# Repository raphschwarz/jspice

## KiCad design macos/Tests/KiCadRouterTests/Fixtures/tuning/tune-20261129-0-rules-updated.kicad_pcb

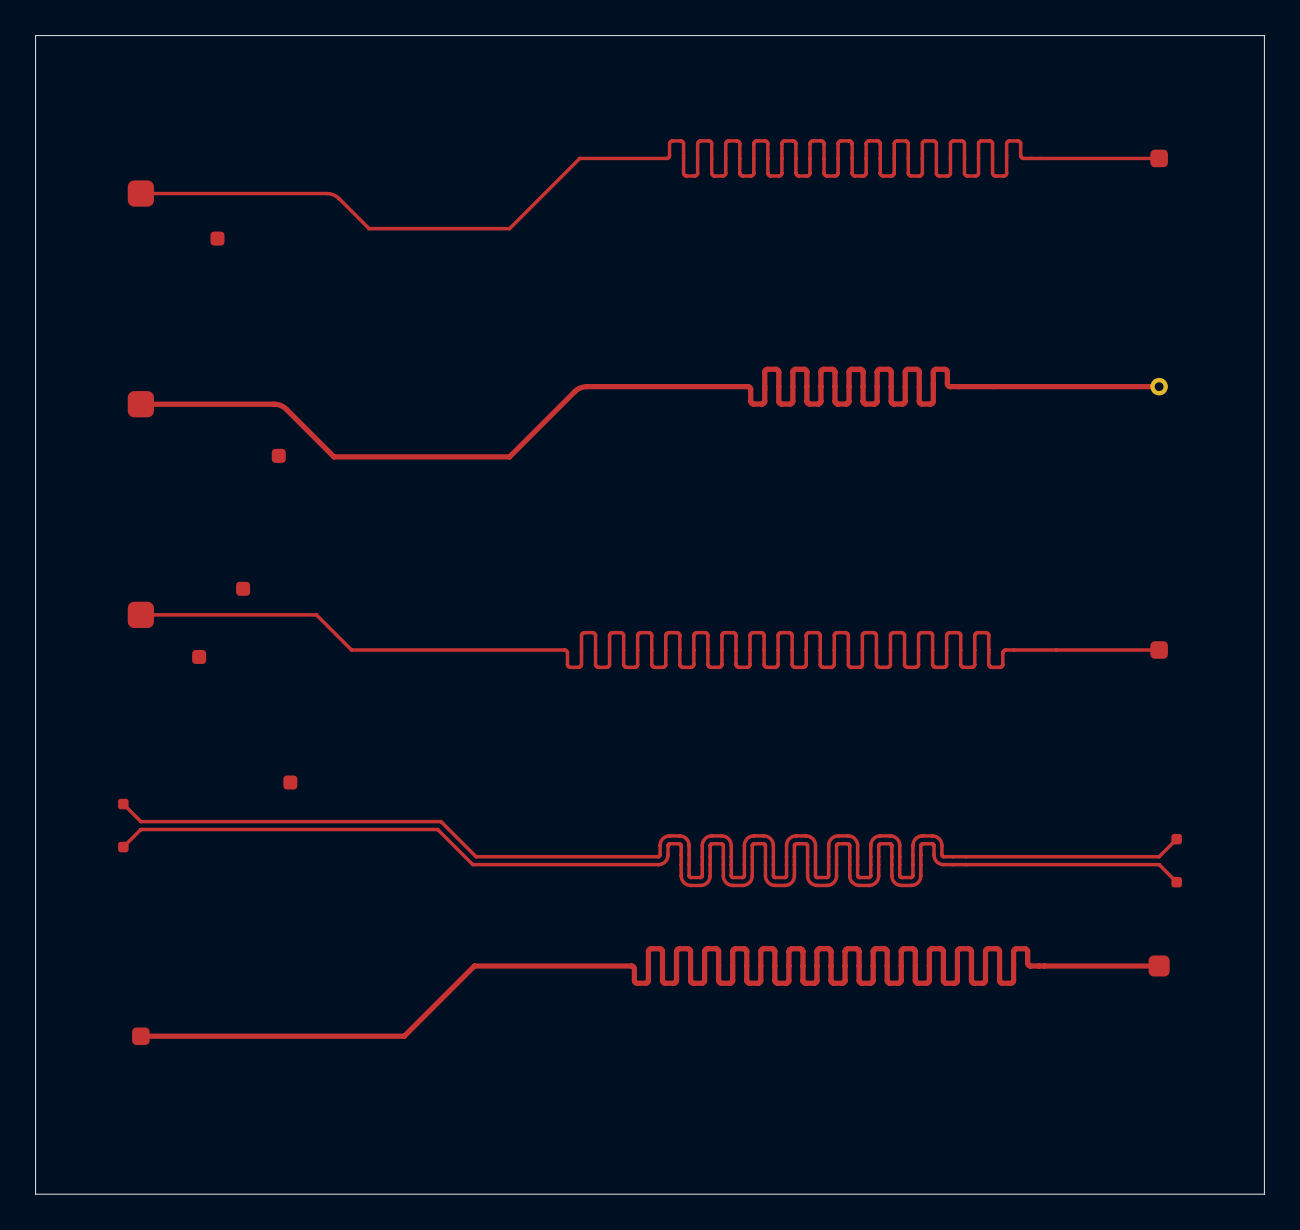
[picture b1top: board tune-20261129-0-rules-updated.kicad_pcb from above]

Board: 2 copper layers, 70.0 x 66.0 mm, 17 parts (0 on the bottom side), 6 nets.

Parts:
P1, P5, P15, P19, P23, P34, P38, P42, P49, P53, P57, P61, P65, P69, P83, P87, P91: Pad

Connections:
D4_N: P65.1, P69.1
D4_P: P57.1, P61.1
S1: P1.1, P5.1
S2: P19.1, P23.1
S3: P38.1, P42.1
S5: P87.1, P91.1
